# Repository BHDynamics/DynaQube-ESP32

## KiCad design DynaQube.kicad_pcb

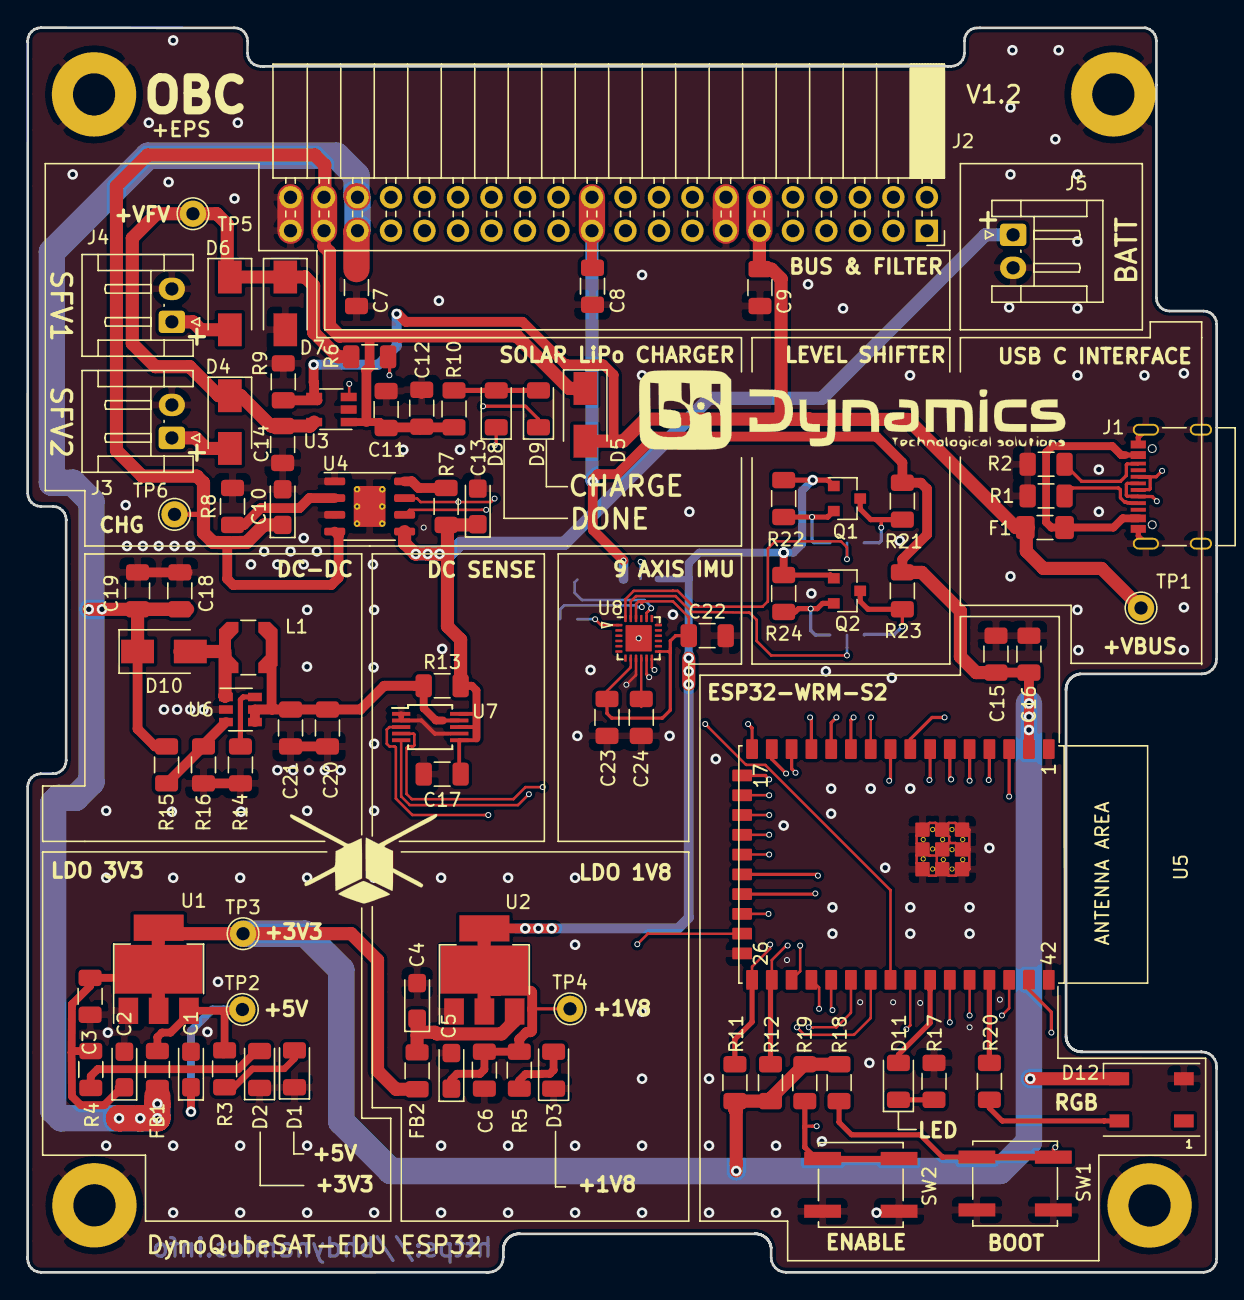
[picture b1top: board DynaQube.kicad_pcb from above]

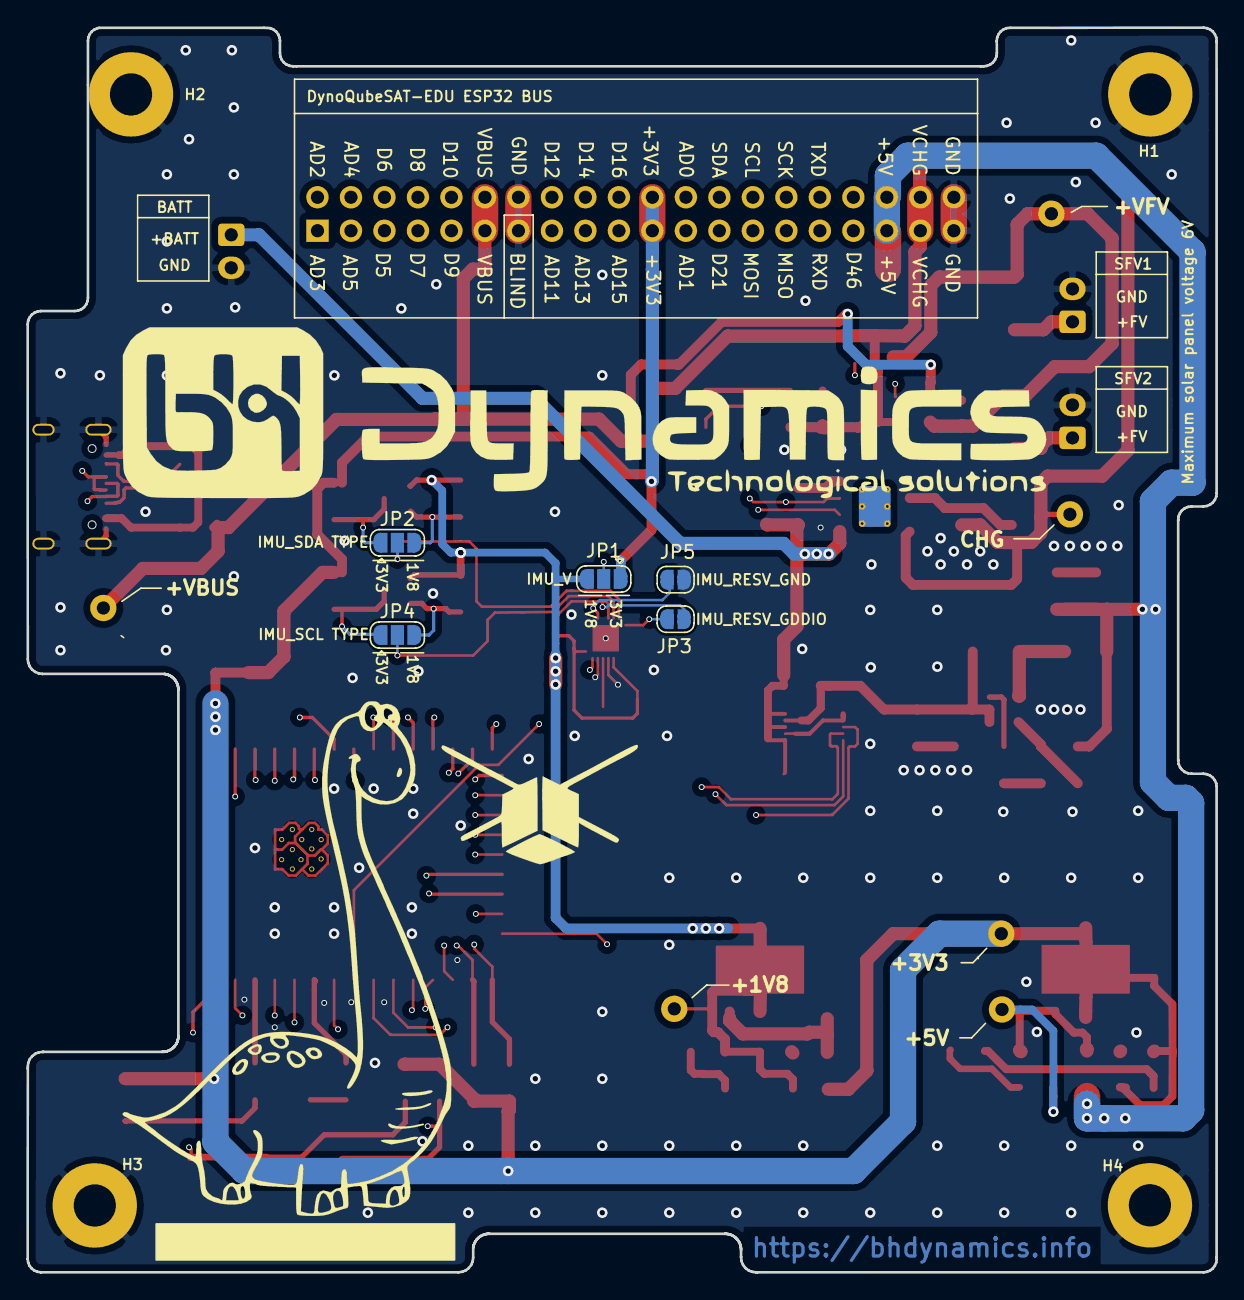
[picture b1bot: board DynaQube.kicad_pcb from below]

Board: 4 copper layers, 90.2 x 94.4 mm, 96 parts (5 on the bottom side), 73 nets.

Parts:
C1, C2, C4, C5, C13: 4.7u; CP_EIA-3216-18_Kemet-A
C3, C6, C7, C8, C9, C11, C16, C17, C19, C20, C22, C23, C24: 100; C_1206_3216Metric
C10: 22uF; CP_EIA-3216-18_Kemet-A
C12, C18, C21: 22uF; C_1206_3216Metric
C14: 1uF; C_1206_3216Metric
C15: 10uF; C_1206_3216Metric
D1: Red; LED_1206_3216Metric
D2, D3: Blue; LED_1206_3216Metric
D4, D5, D6, D7, D10: SS14; D_SMA
D8: DONE; LED_1206_3216Metric
D9: CHRG; LED_1206_3216Metric
D11: TX; LED_1206_3216Metric
D12: RGB; LED_WS2812B_PLCC4_5.0x5.0mm_P3.2mm
F1: 2A; Fuse_1206_3216Metric_Pad1.42x1.75mm_HandSolder
FB1, FB2: 1MH; L_1206_3216Metric
H1, H2, H3, H4: M3; MountingHole_3.2mm_M3_Pad
J1: USB_C_Receptacle_USB2.0; USB_C_Receptacle_Palconn_UTC16-G
J2: Subsystem Interface Connector; PinSocket_2x20_P2.54mm_Horizontal
J3: SFV1; JST_EH_S2B-EH_1x02_P2.50mm_Horizontal
J4: SFV2; JST_EH_S2B-EH_1x02_P2.50mm_Horizontal
J5: BATT; JST_EH_S2B-EH_1x02_P2.50mm_Horizontal
JP1: V_IMU; SolderJumper-3_P1.3mm_Open_RoundedPad1.0x1.5mm
JP2: IMU SDA; SolderJumper-3_P1.3mm_Open_RoundedPad1.0x1.5mm
JP3: VDDIO; SolderJumper-2_P1.3mm_Open_RoundedPad1.0x1.5mm
JP4: IMU SCL; SolderJumper-3_P1.3mm_Open_RoundedPad1.0x1.5mm
JP5: RES_GND; SolderJumper-2_P1.3mm_Open_RoundedPad1.0x1.5mm
L1: 3.3uH; L_Coilcraft_LPS4018
Q1, Q2: BSS138; SOT-23
R1, R2: 5K1; R_1206_3216Metric
R3: 720; R_1206_3216Metric
R4: 470; R_1206_3216Metric
R5: 220; R_1206_3216Metric
R6, R11, R12, R21, R22, R23, R24: 10K; R_1206_3216Metric
R7, R8: xxxx; R_1206_3216Metric
R9, R18, R19: 100K; R_1206_3216Metric
R10: 330; R_1206_3216Metric
R13: 0,002; R_1206_3216Metric
R14: 47K; R_1206_3216Metric
R15: 88K; R_1206_3216Metric
R16: 12K; R_1206_3216Metric
R17: 1K; R_1206_3216Metric
R20: 510; R_1206_3216Metric
SW1: BOOT; SW_Push_1P1T_NO_CK_KSC7xxJ
SW2: ENABLE; SW_Push_1P1T_NO_CK_KSC7xxJ
TP1: VBUS; TestPoint_THTPad_D2.0mm_Drill1.0mm
TP2: 5V; TestPoint_THTPad_D2.0mm_Drill1.0mm
TP3: 3V3; TestPoint_THTPad_D2.0mm_Drill1.0mm
TP4: 1V8; TestPoint_THTPad_D2.0mm_Drill1.0mm
TP5: VFV; TestPoint_THTPad_D2.0mm_Drill1.0mm
TP6: VCHG; TestPoint_THTPad_D2.0mm_Drill1.0mm
U1: LD1117S33CTR; SOT-223-3_TabPin2
U2: LD1117S18CTR; SOT-223-3_TabPin2
U3: AP22811BW5; TSOT-23-5
U4: CN3063; HSOP-8-1EP_3.9x4.9mm_P1.27mm_EP2.41x3.1mm_ThermalVias
U5: ESP32-S2-WROOM; esp32-s2-wrooom
U6: FP6291; SOT-23-6
U7: INA226; MSOP-10_3x3mm_P0.5mm
U8: ICM-20948; InvenSense_QFN-24_3x3mm_P0.4mm

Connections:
/1V8: C5.1, C6.1, JP1.3, Q1.1, Q2.1, R5.1, R22.1, R24.1, TP4.1, U2.2
/3V3: C2.1, C3.1, C8.1, C15.1, C16.1, D12.3, FB2.2, J2.21, J2.22, JP1.1, R4.1, R11.1, R12.1, R18.1, R19.1, R21.1, R23.1, TP3.1, U1.2, U5.2
/5V: C7.1, C18.1, C19.1, D10.1, FB1.2, J2.35, J2.36, R15.2
/AD0: J2.24, U5.20
/AD1: J2.23, U5.21
/AD2: J2.2, U5.4
/AD3: J2.1, U5.5
/AD4: J2.4, U5.6
/AD5: J2.3, U5.7
/BOOT0: R19.2, SW2.2, U5.3
/D5: J2.5, U5.8
/D6: J2.6, U5.9
/D7: J2.7, U5.10
/D8: J2.8, U5.11
/D9: J2.9, U5.12
/D10: J2.10, U5.13
/D11: J2.15, U5.14
/D12: J2.16, U5.15
/D13: J2.17, U5.16
/D14: J2.18, U5.17
/D15: J2.19, U5.18
/D16: J2.20, U5.19
/D21: J2.25, U5.24
/D46: J2.33, U5.40
/D+: J1.A6, J1.B6, U5.23
/D-: J1.A7, J1.B7, U5.22
/ENA: R18.2, SW1.2, U5.41
/IMU_INT: U5.34, U8.12
/IN_SENSE: C13.1, C17.1, J5.1, R7.1, R13.1, U4.5, U7.6, U7.8, U7.10
/LED: D11.2, U5.36
/MISO: J2.29, U5.31
/MOSI: J2.27, U5.29
/NEOPIX: R20.1, U5.39
/OUT_SENSE: C20.1, C21.1, L1.1, R13.2, U6.4, U6.5, U7.9
/POWER_ALERT: U5.35, U7.3
/Panel: R6.1, U3.3, U5.25
/RXD0: J2.31, U5.38
/SCK: J2.30, U5.30
/SCL: J2.28, JP4.1, Q2.3, R12.2, R23.2, U5.28, U7.5
/SCL_1V8: JP4.3, Q2.2, R24.2
/SCL_IMU: JP4.2, U8.23
/SDA: J2.26, JP2.1, Q1.3, R11.2, R21.2, U5.27, U7.4
/SDA_1V8: JP2.3, Q1.2, R22.2
/SDA_IMU: JP2.2, U8.24
/TXD0: J2.32, U5.37
/VBUS: C9.1, D5.2, F1.2, J2.11, J2.12, R9.2, TP1.1, U3.4
/VCHG: C10.1, C11.1, C12.1, D5.1, J2.37, J2.38, R10.2, TP6.1, U3.1, U4.4
/VFV: C14.1, D4.1, D6.1, D7.1, R6.2, TP5.1, U3.5
/V_IMU: C22.1, C23.1, JP1.2, JP3.1, U8.8, U8.13, U8.22
/`CHARGE: D9.1, U4.7, U5.32
/`DONE: D8.1, U4.6, U5.33
GND: C1.2, C2.2, C3.2, C4.2, C5.2, C6.2, C7.2, C8.2, C9.2, C10.2, C11.2, C12.2, C13.2, C14.2, C15.2, C16.2, C17.2, C18.2, C19.2, C20.2, C21.2, C22.2, C23.2, C24.2, D1.1, D2.1, D3.1, D7.2, D12.2, H1.1, H2.1, H3.1, H4.1, J1.A1, J1.A12, J1.B1, J1.B12, J1.S1, J2.13, J2.14, J2.39, J2.40, J3.2, J4.2, J5.2, JP5.2, R1.1, R2.1, R8.1, R9.1, R14.1, R16.1, R17.2, SW1.1, SW2.1, U1.1, U2.1, U3.2, U4.1, U4.3, U4.9, U5.1, U5.26, U5.42, U5.43, U6.2, U7.1, U7.2, U7.7, U8.9, U8.11, U8.18
unnamed: C1.1, FB1.1, R3.1, TP2.1, U1.3
unnamed: C4.1, FB2.1, U2.3
unnamed: C24.1, U8.10
unnamed: D1.2, R3.2
unnamed: D2.2, R4.2
unnamed: D3.2, R5.2
unnamed: D4.2, J3.1
unnamed: D6.2, J4.1
unnamed: D8.2, D9.2, R10.1
unnamed: D10.2, L1.2, U6.1
unnamed: D11.1, R17.1
unnamed: D12.4, R20.2
unnamed: F1.1, J1.A4, J1.A9, J1.B4, J1.B9
unnamed: J1.A5, R1.2
unnamed: J1.B5, R2.2
unnamed: JP3.2, U8.1
unnamed: JP5.1, U8.20
unnamed: R7.2, U4.8
unnamed: R8.2, U4.2
unnamed: R14.2, U6.6
unnamed: R15.1, R16.2, U6.3
